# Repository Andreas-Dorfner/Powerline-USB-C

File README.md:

# Powerline-USB-C
Powerline is a small 3HP Front Entry USB C Eurorack power supply.

## Repository Layout
The Frontpanel and main PCB have a Kicad project with footprint and symbol libraries.
The main PCB also includes a 3D render of the Frontpanel as a Footprint
## Specs
- 12V 1000mA
- -12V 300mA
- 5V 1000mA
## Features
Powerline uses the cheap and readily available CH224k IC to get 20V over USB-C PD. The power brick should supply at least 2A of current at that voltage (40W Charger and above should be fine).
The 20V then gets regulated to a dual +/-12V and 5V supply by two N7812-1C and an N7805-1C and can be accessed by one 16-pin Power header. You can also omit the 5V rail and solder a 10pin header if none of your modules need 5V.
Powerline uses a single LED powered by the 12V rail to indicate power.
The PCBs are designed to jlcpcbs 2 Layer design capabilities to be compatible with most cheap PCB services.
## Parts List
The only difficult-to-source parts are the USB-C connector and regulator ICs. I got both from Digikey.
I also recommend sourcing the CH224k from a reputable supplier like LCSC to avoid broken parts.
You also need two M2 5mm standoffs and 4 M2 screws that fit the standoffs (max. 4mm) to assemble the Module.

|Part Number|Value|Information|
|---|---|---|
|C1, C8|0805 1uF 50V X7R|Decoupling Capacitors|
|C2, C4, C6|1210 10uF 50V X7R|Input Cap for the regulator|
|C3, C5, C7|1210 22uF 25V X7R|Output cap for the regulator|
|D1|3mm LED|3mm radial LED with a nice color|
|J1|MC-802YC-H105|Female USB-C connector|
|J2|Power header|A 02x08 2.54mm pin spacing vertical through hole pin header|
|L1|1210 10uH|Look out for a rated current of above 600mA|
|R1|0603 5k1|Current limiting resistor for the LED: if it's too bright, pick a higher resistance|
|R2|0604 10k|VBUS sense resistor|
|U1|CH224K|The PD trigger IC|
|U2, U3|N7912-1C|+/-12V regulators|
|U4|N7805-1C|5V regulator|
|U5|HT7533-1|3.3V regulator|
|Standoffs|m2 5-7.5mm|You need 2 Standoffs and 4 screws to mount the Module to its front plate
## Build Guide
The PCB doesn't include any Thermal reliefs so that soldering can be tricky with a weak iron or small tip. I did everything with a 60W and 4mm Bevel Tip on a TS100 with extra Flux. You do not need additional equipment as the CH224K is solderable from the bottom. I used 7.5mm Standoffs, which protects the USB-C connector nicely. I would recommend soldering the USB-C connector last.

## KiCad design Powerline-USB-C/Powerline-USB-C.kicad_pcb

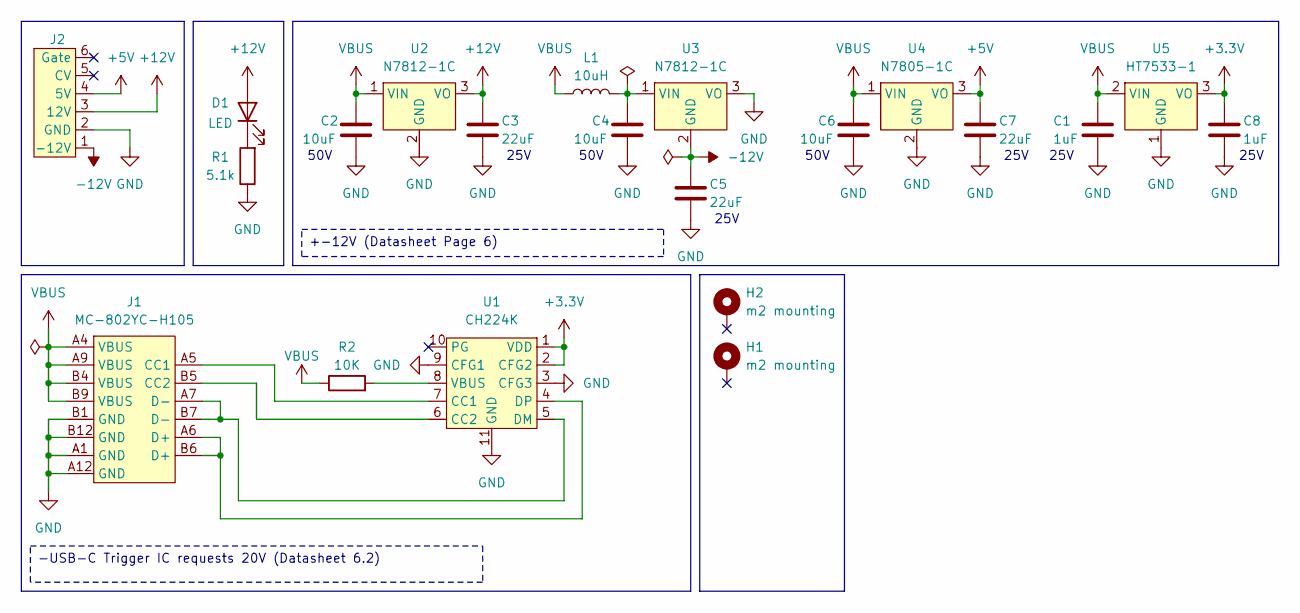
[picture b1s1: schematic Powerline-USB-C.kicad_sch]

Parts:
C1, C8: 1uF; C_0805_2012Metric
C2, C4, C6: 10uF; C_1210_3225Metric
C3, C5, C7: 22uF; C_1210_3225Metric
D1: LED; LED_D3.0mm
H1, H2: m2 mounting; MountingHole_2.2mm_M2_DIN965_Pad
J1: MC-802YC-H105; USB-C
J2: Keyed_16pin_Powerheader
L1: 10uH; L_1210_3225Metric
R1: 5.1k; C_0603_1608Metric
R2: 10K; R_0603_1608Metric
U1: CH224K; CH224k
U2, U3: N7812-1C
U4: N7805-1C; N7812-1C
U5: HT7533-1

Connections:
+3.3V: C8.1, U1.1 (VDD), U1.2 (CFG2), U5.3 (VO)
+5V: C7.1, J2.4 (5V), U4.3 (VO)
+12V: C3.1, D1.2 (A), J2.3 (12V), U2.3 (VO)
-12V: C5.1, J2.1 (-12V), U3.2 (GND)
GND: C1.2, C2.2, C3.2, C4.2, C5.2, C6.2, C7.2, C8.2, J1.A1 (GND), J1.A12 (GND), J1.B1 (GND), J1.B12 (GND), J2.2 (GND), R1.1, U1.3 (CFG3), U1.9 (CFG1), U1.11 (GND), U2.2 (GND), U3.3 (VO), U4.2 (GND), U5.1 (GND)
unnamed: D1.1 (K), R1.2
unnamed: J1.A5 (CC1), U1.7 (CC1)
unnamed: J1.B5 (CC2), U1.6 (CC2)
unnamed: J1.A7 (D-), J1.B7 (D-), U1.5 (DM)
unnamed: J1.A6 (D+), J1.B6 (D+), U1.4 (DP)
unnamed: R2.2, U1.8 (VBUS)
unnamed: C4.1, L1.2, U3.1 (VIN)
VBUS: C1.1, C2.1, C6.1, J1.A4 (VBUS), J1.A9 (VBUS), J1.B4 (VBUS), J1.B9 (VBUS), L1.1, R2.1, U2.1 (VIN), U4.1 (VIN), U5.2 (VIN)

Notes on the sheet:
25V
50V
-USB-C Trigger IC requests 20V (Datasheet 6.2)
+-12V (Datasheet Page 6)

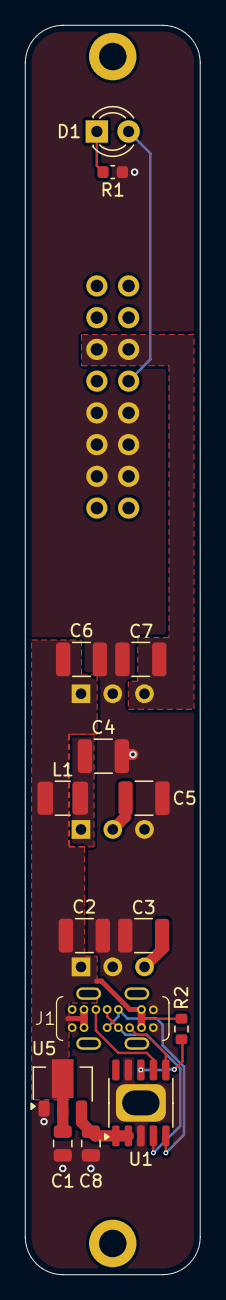
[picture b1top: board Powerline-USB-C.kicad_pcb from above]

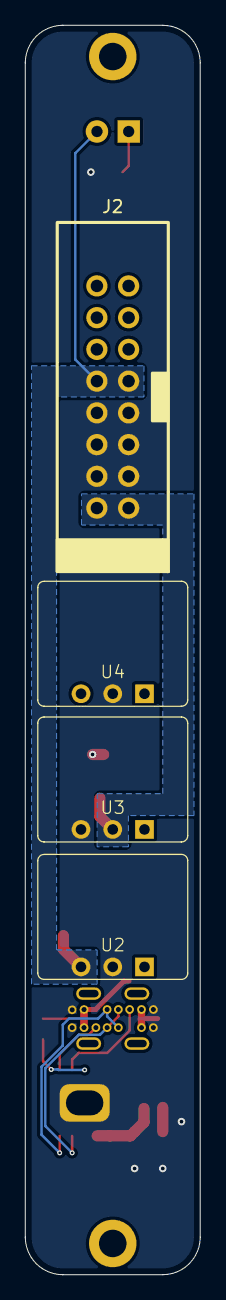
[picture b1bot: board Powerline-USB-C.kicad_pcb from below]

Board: 2 copper layers, 14.0 x 100.0 mm, 21 parts (4 on the bottom side), 13 nets.

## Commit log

2024-08-26 Hardware commit
    Main PCB and Frontpanel Version 0.1
2024-08-26 Aktualisieren von README.md
2024-08-27 minor hardware revision for main PCB
    -changed two 10pin headers for singele 16pin header
    -added 5V rail
2024-08-27 Added 3D renders and fixed file structure
2024-08-27 Update README.md
    Fixed Parts List and added 3D render
2024-08-27 Update README.md
    Added 3D renders (this time for real)
2024-08-27 Changed 3D render
2024-08-27 Update README.md
    Changed Layout
2024-08-27 Updated 3D-render
2024-08-27 house keeping
2025-04-14 update to kicad9
2025-04-14 Update to Kicad 9
2025-05-02 tidying
